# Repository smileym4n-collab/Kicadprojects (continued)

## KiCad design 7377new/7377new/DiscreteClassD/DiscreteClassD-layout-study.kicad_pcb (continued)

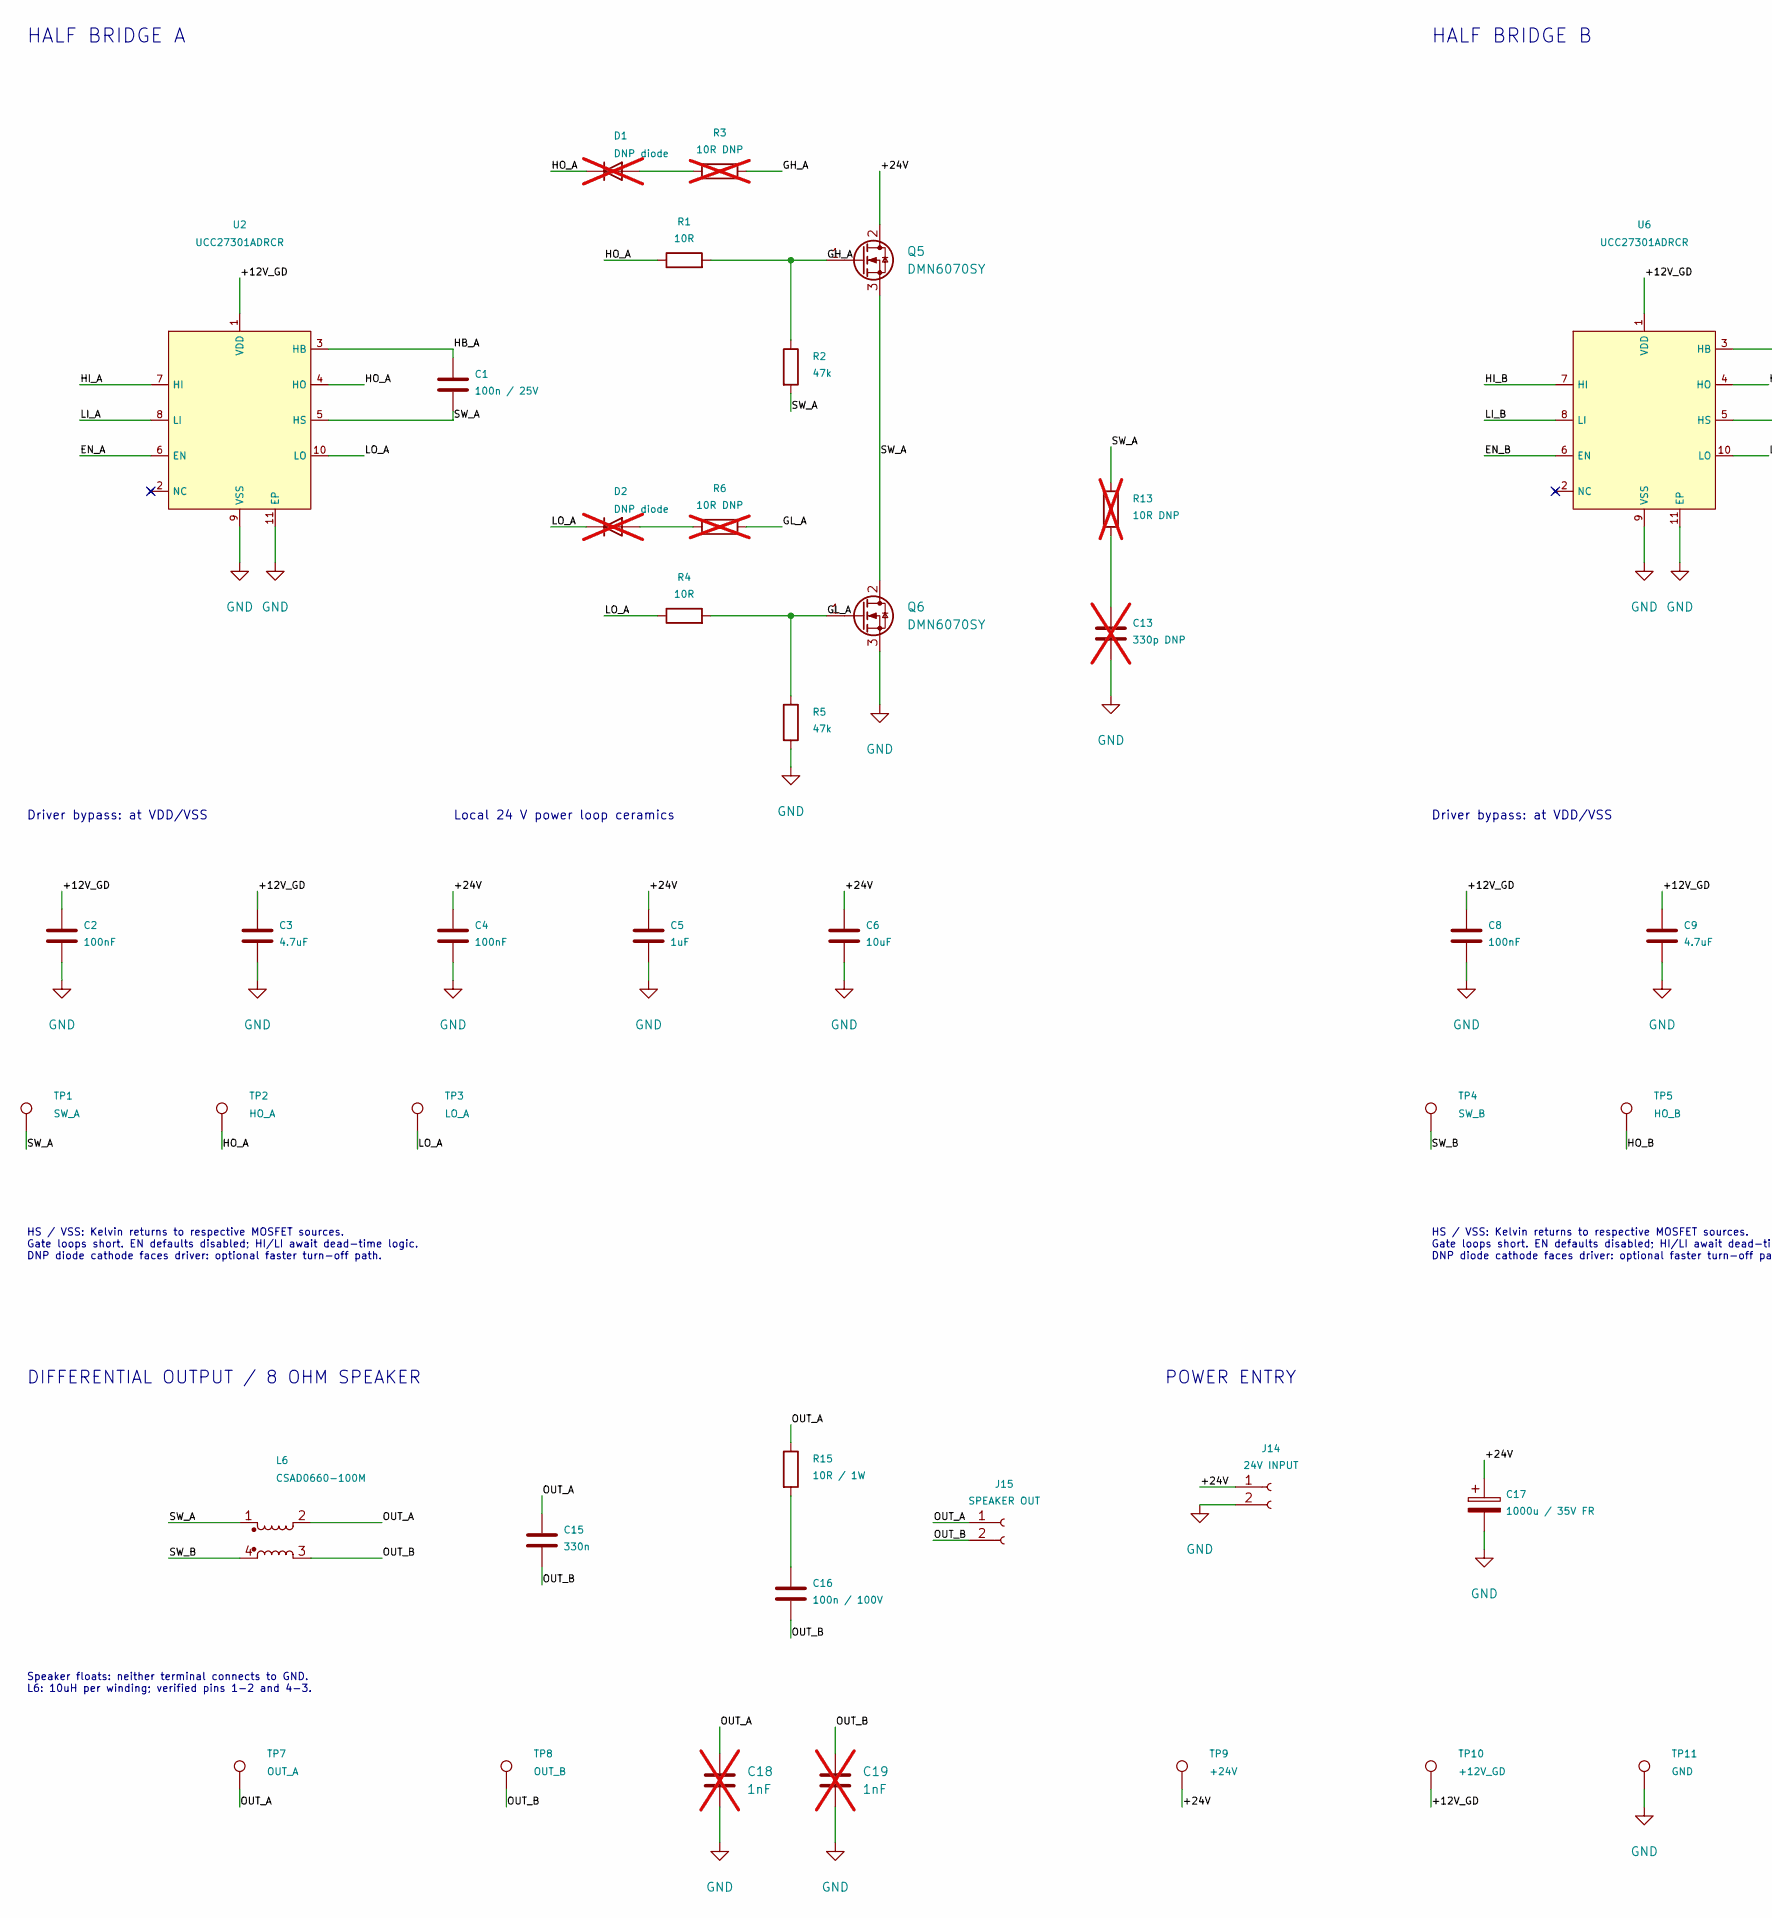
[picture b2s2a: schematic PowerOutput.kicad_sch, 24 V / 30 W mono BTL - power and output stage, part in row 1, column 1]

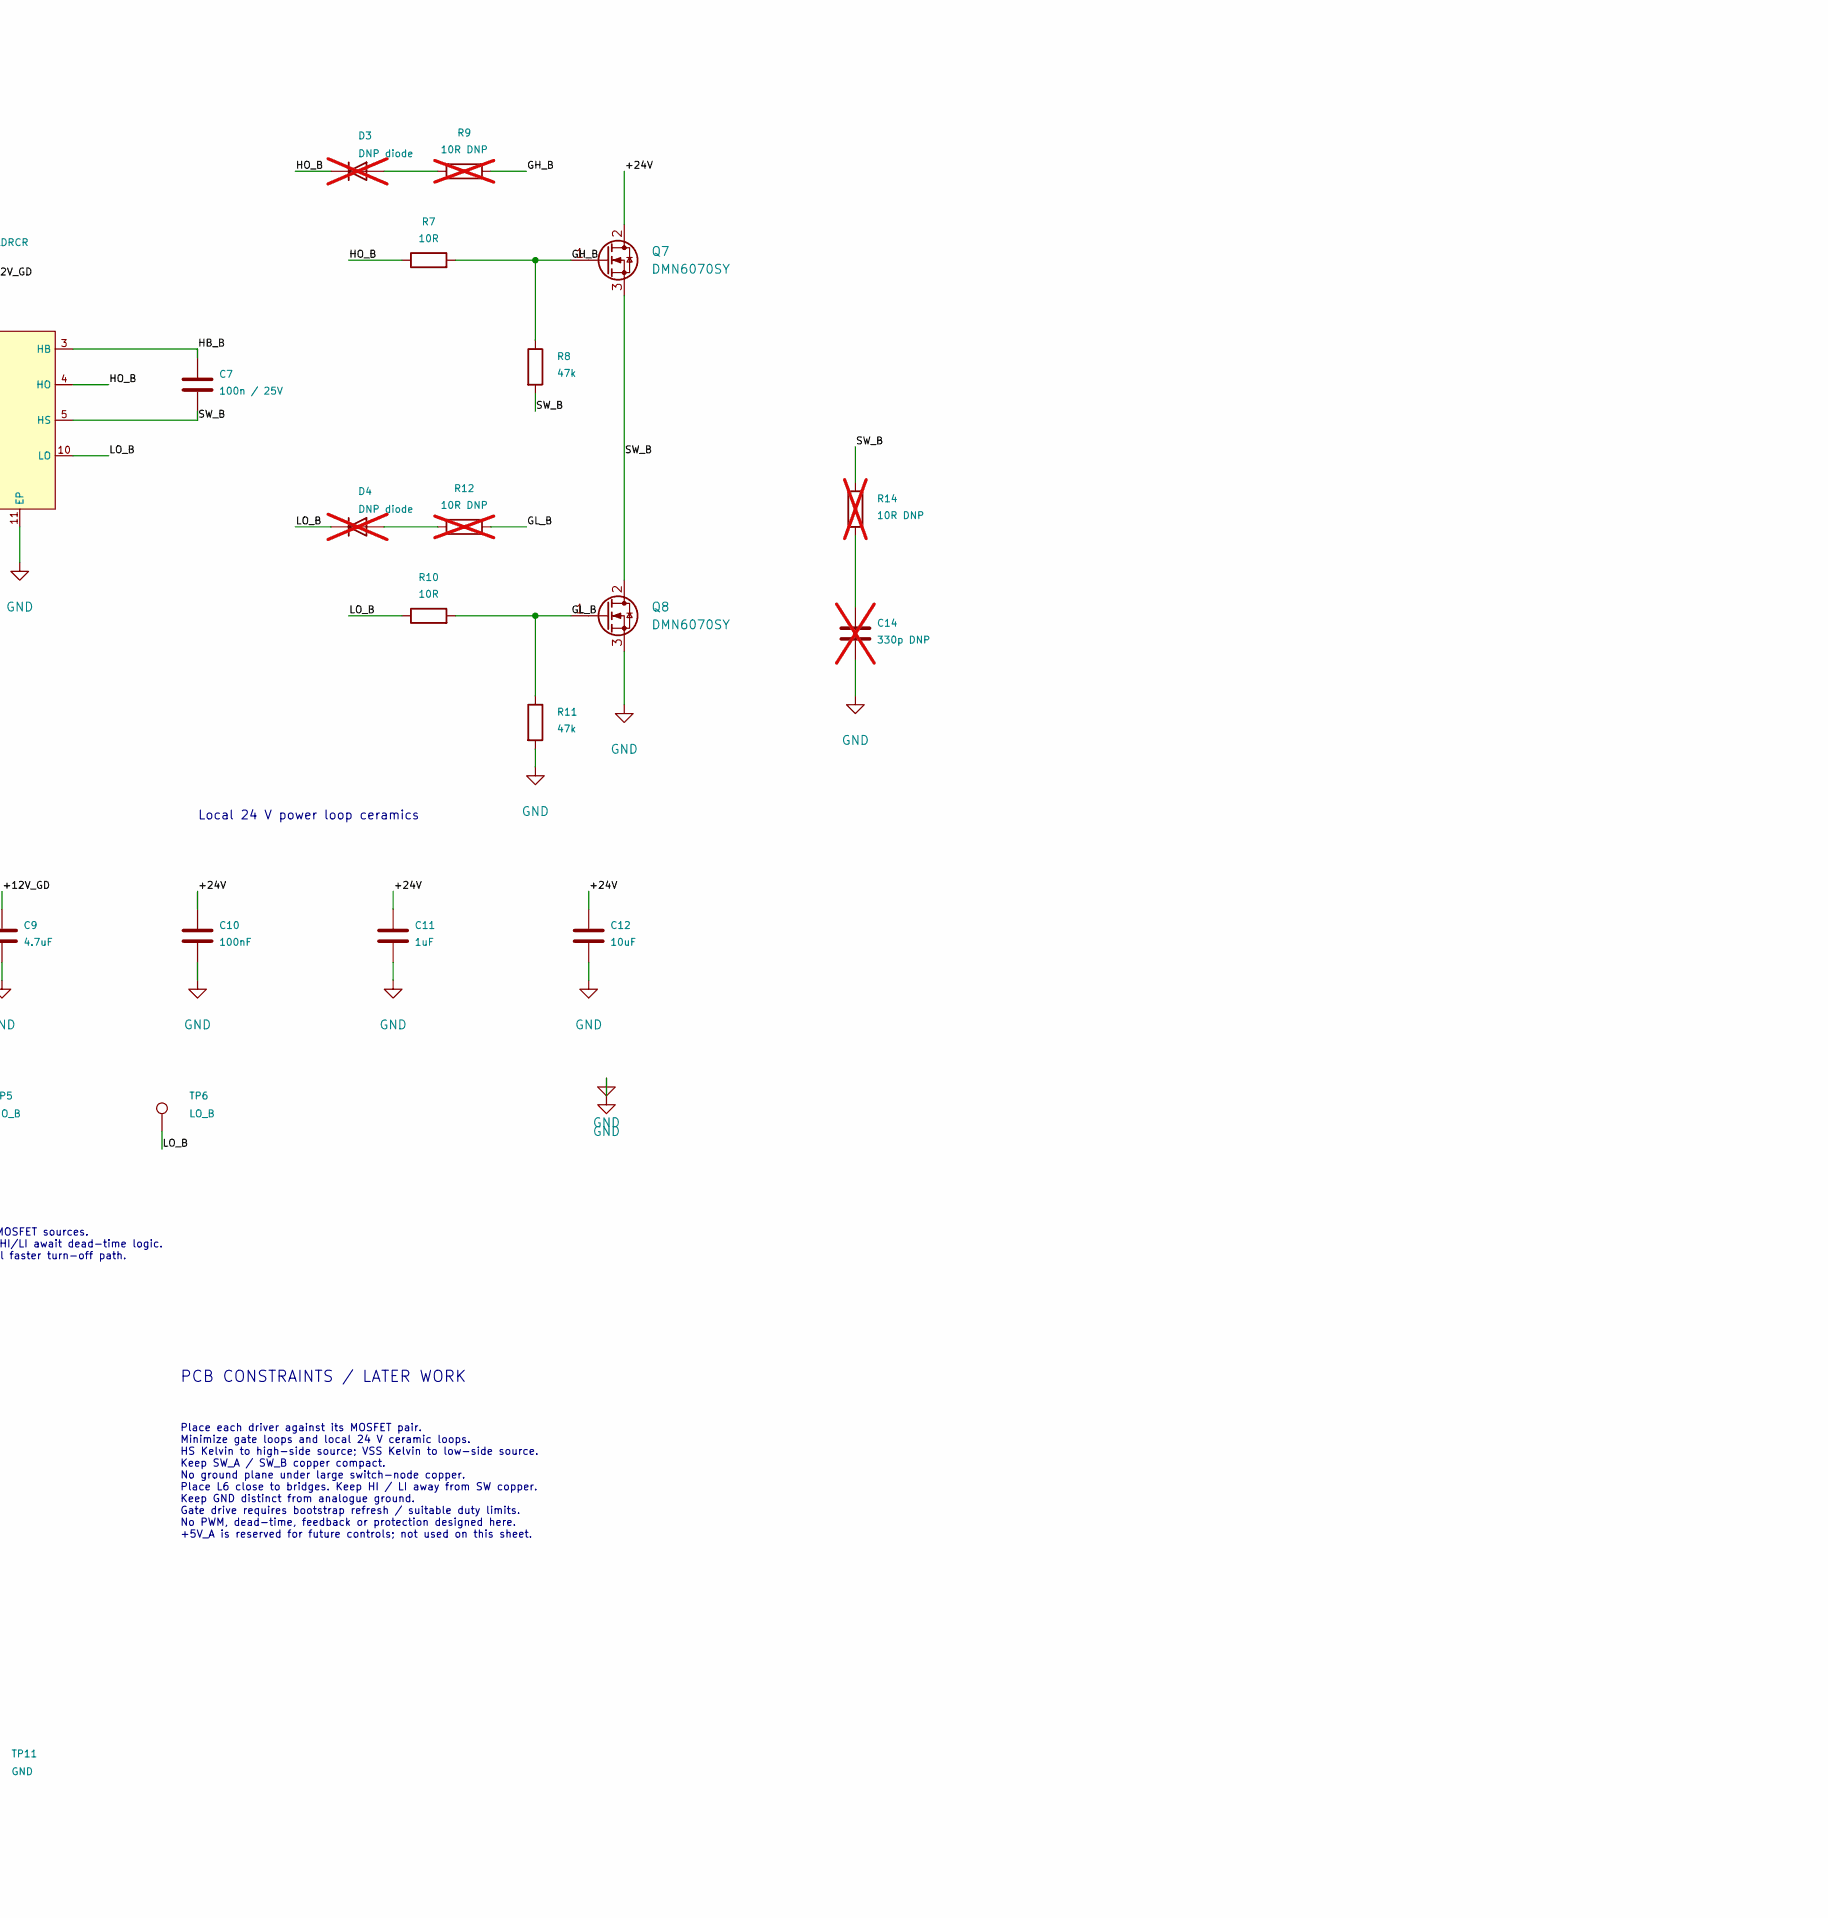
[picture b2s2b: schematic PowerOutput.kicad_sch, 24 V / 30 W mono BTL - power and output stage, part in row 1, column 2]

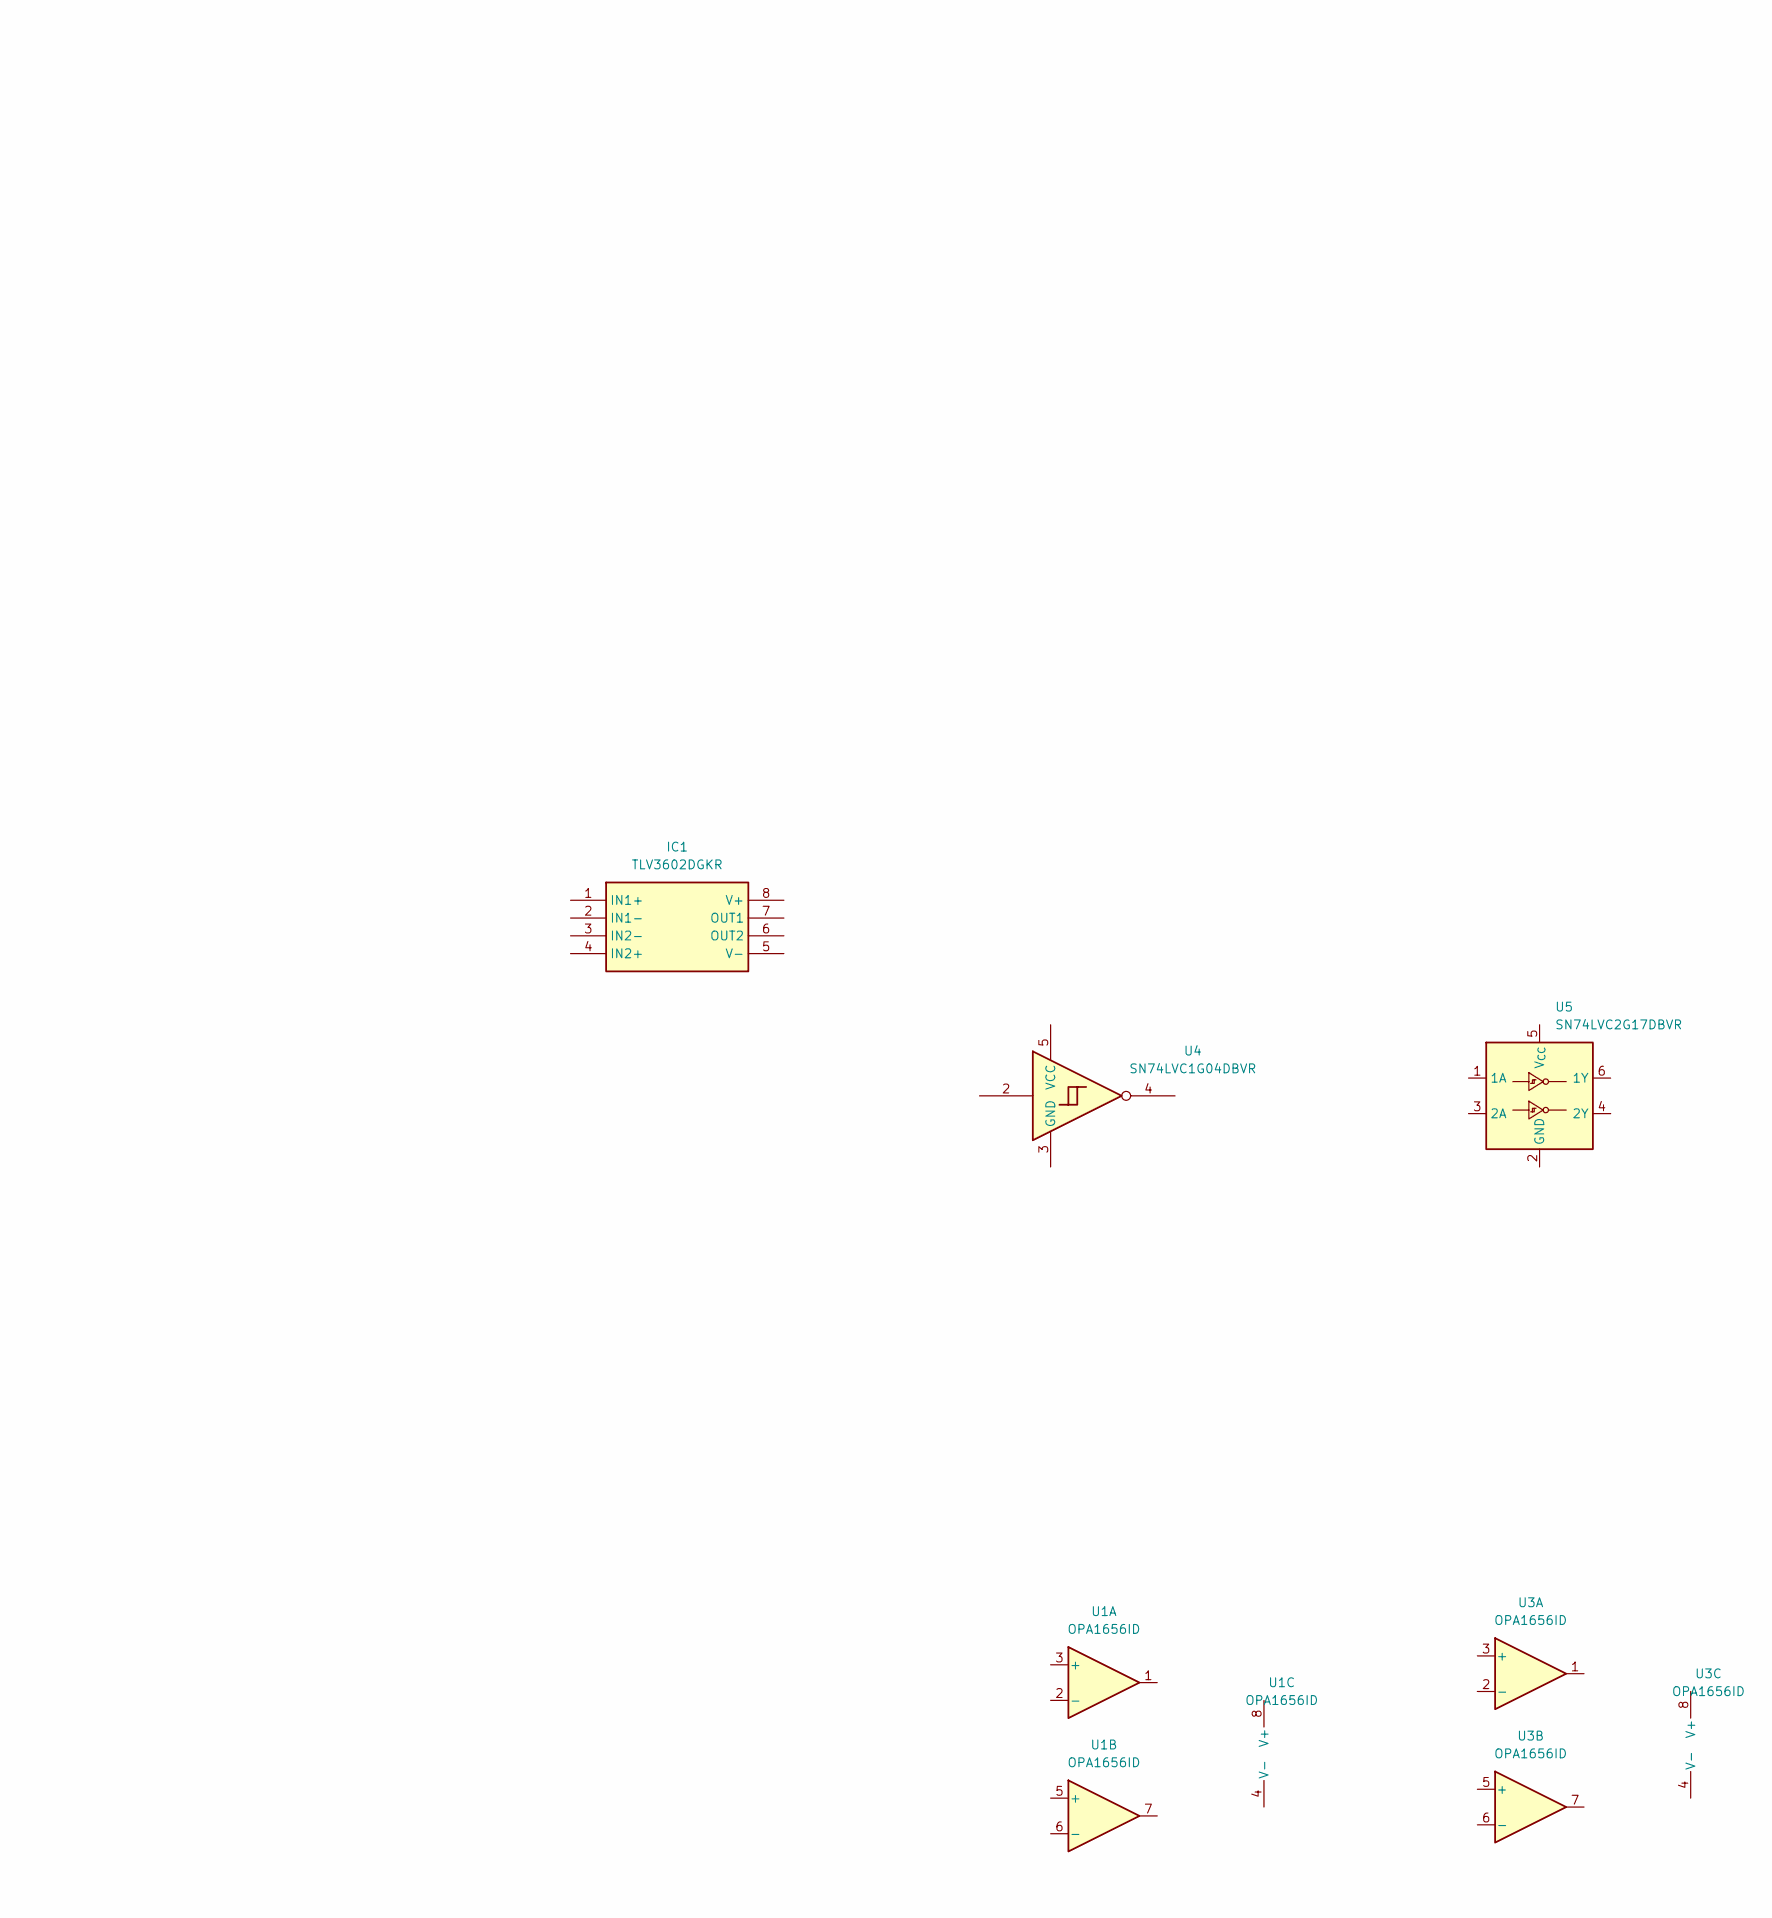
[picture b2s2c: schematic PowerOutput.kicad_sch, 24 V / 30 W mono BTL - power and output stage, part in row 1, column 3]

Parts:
C1, C7: 100n / 25V; C_0805_2012Metric
C2, C8: 100nF; C_0805_2012Metric
C3, C9: 4.7uF; C_0805_2012Metric
C4, C10: 100nF; C_1206_3216Metric_Pad1.33x1.80mm_HandSolder
C5, C11: 1uF; C_1206_3216Metric_Pad1.33x1.80mm_HandSolder
C6, C12: 10uF; C_1206_3216Metric_Pad1.33x1.80mm_HandSolder
C13, C14: 330p DNP; C_0805_2012Metric; Voltage 100V; not fitted
C15: 330n; C_Rect_L7.2mm_W3.0mm_P5.00mm_FKS2_FKP2_MKS2_MKP2; Voltage 100V
C16: 100n / 100V; C_1206_3216Metric_Pad1.33x1.80mm_HandSolder
C17: 1000u / 35V FR; CP_Radial_D12.5mm_P5.00mm; MPN EEUFR1V102
C18, C19: 1nF; C_0805_2012Metric_Pad1.18x1.45mm_HandSolder; not fitted
D1, D2, D3, D4: DNP diode; D_SOD-123; not fitted
IC1: TLV3602DGKR; VSSOP-8_3x3mm_P0.65mm; Mouser Part Number 595-TLV3602DGKR
J14: 24V INPUT; Molex_KK-396_A-41791-0002_1x02_P3.96mm_Vertical
J15: SPEAKER OUT; Molex_KK-396_A-41791-0002_1x02_P3.96mm_Vertical
L6: CSAD0660-100M
Q5, Q6, Q7, Q8: DMN6070SY; SOT-89-3
R1, R4, R7, R10: 10R; R_0805_2012Metric
R2, R5, R8, R11: 47k; R_0805_2012Metric
R3, R6, R9, R12: 10R DNP; R_0805_2012Metric; not fitted
R13, R14: 10R DNP; R_1206_3216Metric; not fitted
R15: 10R / 1W; R_2512_6332Metric
TP1: SW_A; TestPoint_Pad_D1.5mm
TP2: HO_A; TestPoint_Pad_D1.5mm
TP3: LO_A; TestPoint_Pad_D1.5mm
TP4: SW_B; TestPoint_Pad_D1.5mm
TP5: HO_B; TestPoint_Pad_D1.5mm
TP6: LO_B; TestPoint_Pad_D1.5mm
TP7: OUT_A; TestPoint_Pad_D1.5mm
TP8: OUT_B; TestPoint_Pad_D1.5mm
TP9: +24V; TestPoint_Pad_D1.5mm
TP10: +12V_GD; TestPoint_Pad_D1.5mm
TP11: GND; TestPoint_Pad_D1.5mm
U1, U3: OPA1656ID; SOIC-8_3.9x4.9mm_P1.27mm
U2, U6: UCC27301ADRCR; VSON-10-1EP_3x3mm_P0.5mm_EP1.65x2.4mm
U4: SN74LVC1G04DBVR; SOT-553
U5: SN74LVC2G17DBVR; SOT-23-6

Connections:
+5V_A: U4.5 (VCC), U5.5 (VCC); also elsewhere on the board
+12V_A: U1.8 (V+), U3.8 (V+); also elsewhere on the board
+12V_GD: C2.1, C3.1, C8.1, C9.1, TP10.1 (1_1), U2.1 (VDD), U6.1 (VDD); also elsewhere on the board
+24V: C4.1, C5.1, C6.1, C10.1, C11.1, C12.1, C17.1, J14.1, Q5.2 (D), Q7.2 (D), TP9.1; also elsewhere on the board
/LEFT OUTPUT/OUT_A: C15.1, C18.1, J15.1, L6.2, R15.1, TP7.1 (1_1)
/LEFT OUTPUT/OUT_B: C15.2, C16.2, C19.1, J15.2, L6.3, TP8.1 (1_1)
/LEFT OUTPUT/SW_A: C1.2, L6.1, Q5.3 (S), Q6.2 (D), R2.2, R13.1, TP1.1 (1_1), U2.5 (HS)
/LEFT OUTPUT/SW_B: C7.2, L6.4, Q7.3 (S), Q8.2 (D), R8.2, R14.1, TP4.1 (1_1), U6.5 (HS)
/PWM_L: U4.2; also elsewhere on the board
/TRIANGLE_400K: U3.7; also elsewhere on the board
/VREF_2V5: U3.1, U3.2 (-), U3.5 (+); also elsewhere on the board
GND: C2.2, C3.2, C4.2, C5.2, C6.2, C8.2, C9.2, C10.2, C11.2, C12.2, C13.2, C14.2, C17.2, C18.2, C19.2, J14.2, Q6.3 (S), Q8.3 (S), R5.2, R11.2, TP11.1, U1.4 (V-), U2.9 (VSS), U2.11 (EP), U3.4 (V-), U4.3 (GND), U5.2 (GND), U6.9 (VSS), U6.11 (EP); also elsewhere on the board
unnamed: C13.1, R13.2
unnamed: C14.1, R14.2
unnamed: C16.1, R15.2
unnamed: D1.2 (A), R3.1
unnamed: D1.1 (K), R1.1, TP2.1 (1_1), U2.4 (HO)
unnamed: D2.2 (A), R6.1
unnamed: D2.1 (K), R4.1, TP3.1 (1_1), U2.10 (LO)
unnamed: D3.2 (A), R9.1
unnamed: D3.1 (K), R7.1, TP5.1 (1_1), U6.4 (HO)
unnamed: D4.2 (A), R12.1
unnamed: D4.1 (K), R10.1, TP6.1 (1_1), U6.10 (LO)
unnamed 41: U5.1 (1A); also elsewhere on the board
unnamed 42: U5.3 (2A); also elsewhere on the board
unnamed 43: U4.4; also elsewhere on the board
unnamed: Q5.1 (G), R1.2, R2.1, R3.2
unnamed: Q6.1 (G), R4.2, R5.1, R6.2
unnamed: Q7.1 (G), R7.2, R8.1, R9.2
unnamed: Q8.1 (G), R10.2, R11.1, R12.2
unnamed 63: U1.3 (+); also elsewhere on the board
unnamed 64: U1.1, U1.2 (-); also elsewhere on the board
unnamed 65: U1.5 (+); also elsewhere on the board
unnamed 66: U1.6 (-), U1.7; also elsewhere on the board
unnamed: C1.1, U2.3 (HB)
unnamed 68: U3.3 (+); also elsewhere on the board
unnamed 69: U3.6 (-); also elsewhere on the board
unnamed: C7.1, U6.3 (HB)

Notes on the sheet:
HALF BRIDGE A
PCB CONSTRAINTS / LATER WORK
POWER ENTRY
Local 24 V power loop ceramics
HS / VSS: Kelvin returns to respective MOSFET sources. Gate loops short. EN defaults disabled; HI/LI await dead-time logic. DNP diode cathode faces driver: optional faster turn-off path.
Speaker floats: neither terminal connects to GND. L6: 10uH per winding; verified pins 1-2 and 4-3.
HALF BRIDGE B
DIFFERENTIAL OUTPUT / 8 OHM SPEAKER
Driver bypass: at VDD/VSS
Place each driver against its MOSFET pair. Minimize gate loops and local 24 V ceramic loops. HS Kelvin to high-side source; VSS Kelvin to low-side source. Keep SW_A / SW_B copper compact. No ground plane under large switch-node copper. Place L6 close to bridges. Keep HI / LI away from SW copper. Ke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

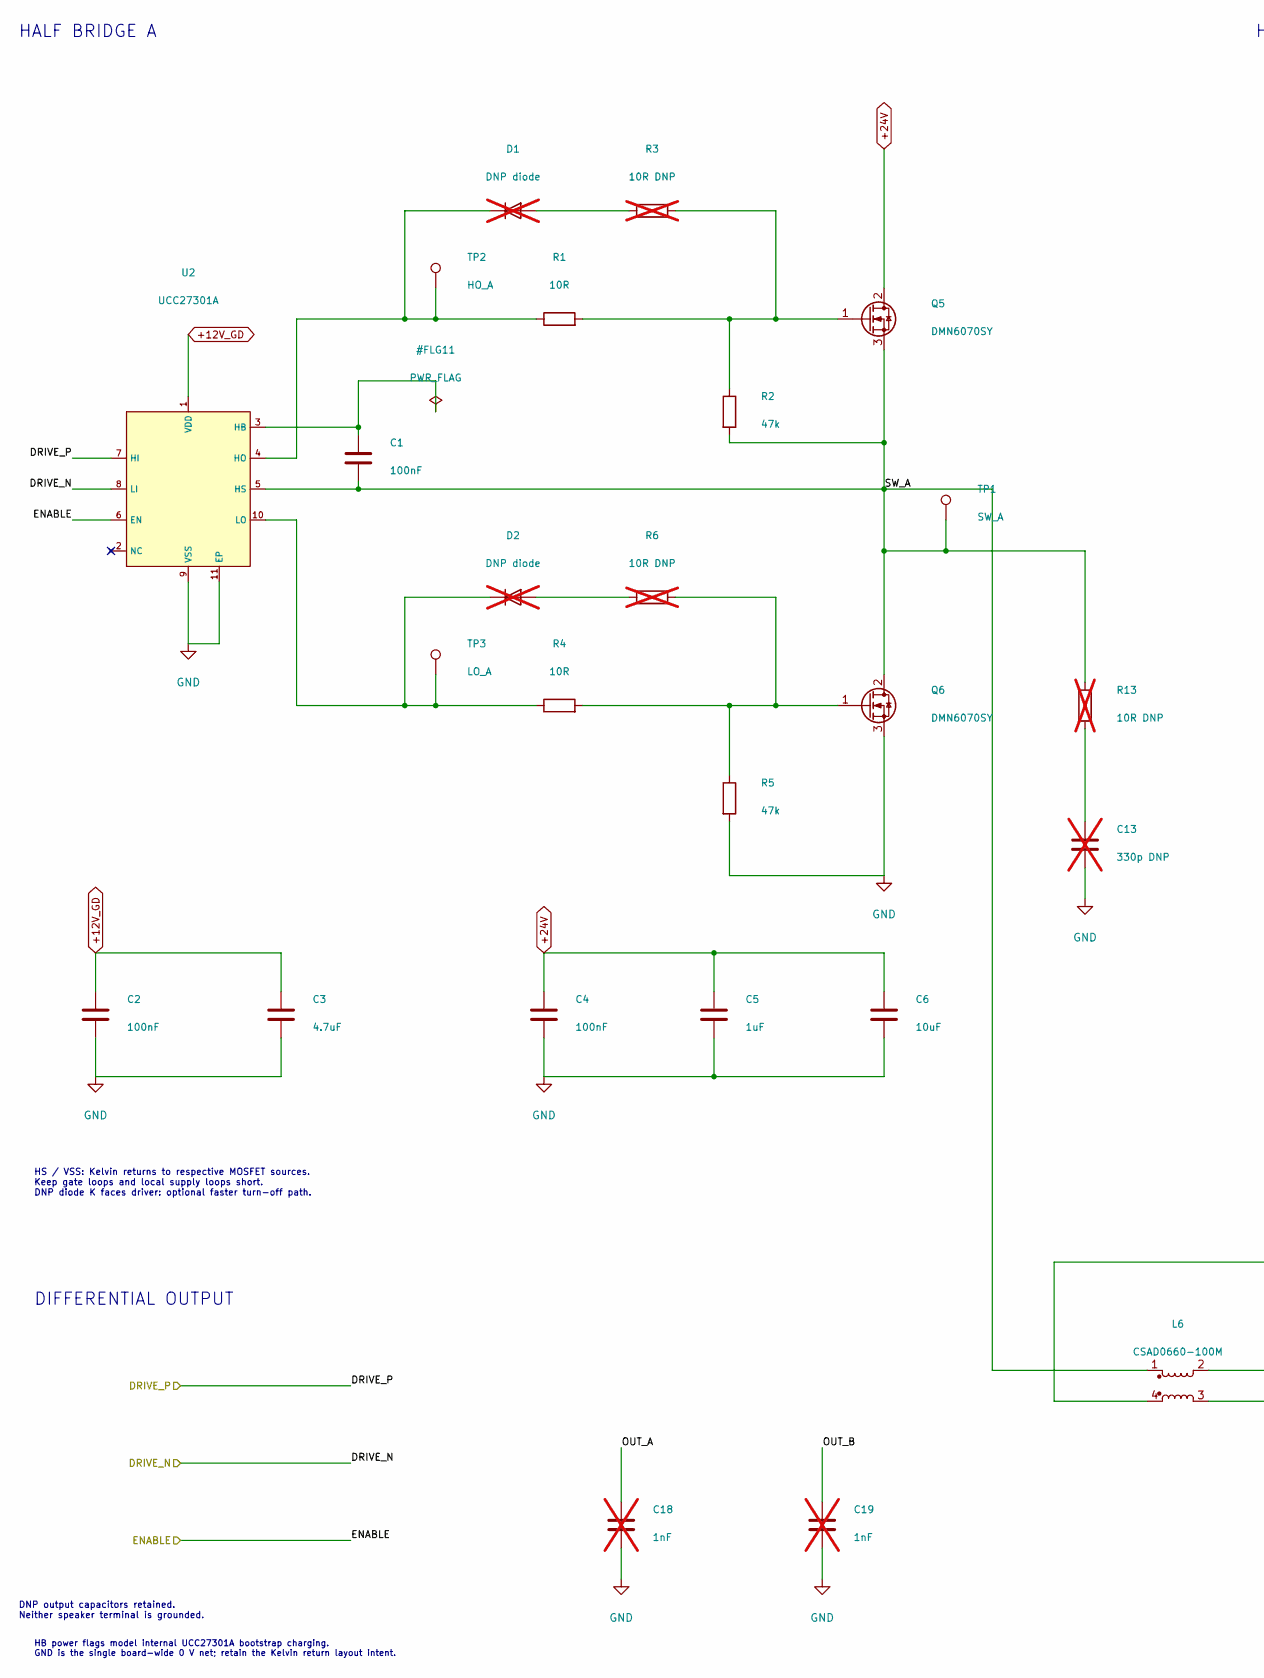
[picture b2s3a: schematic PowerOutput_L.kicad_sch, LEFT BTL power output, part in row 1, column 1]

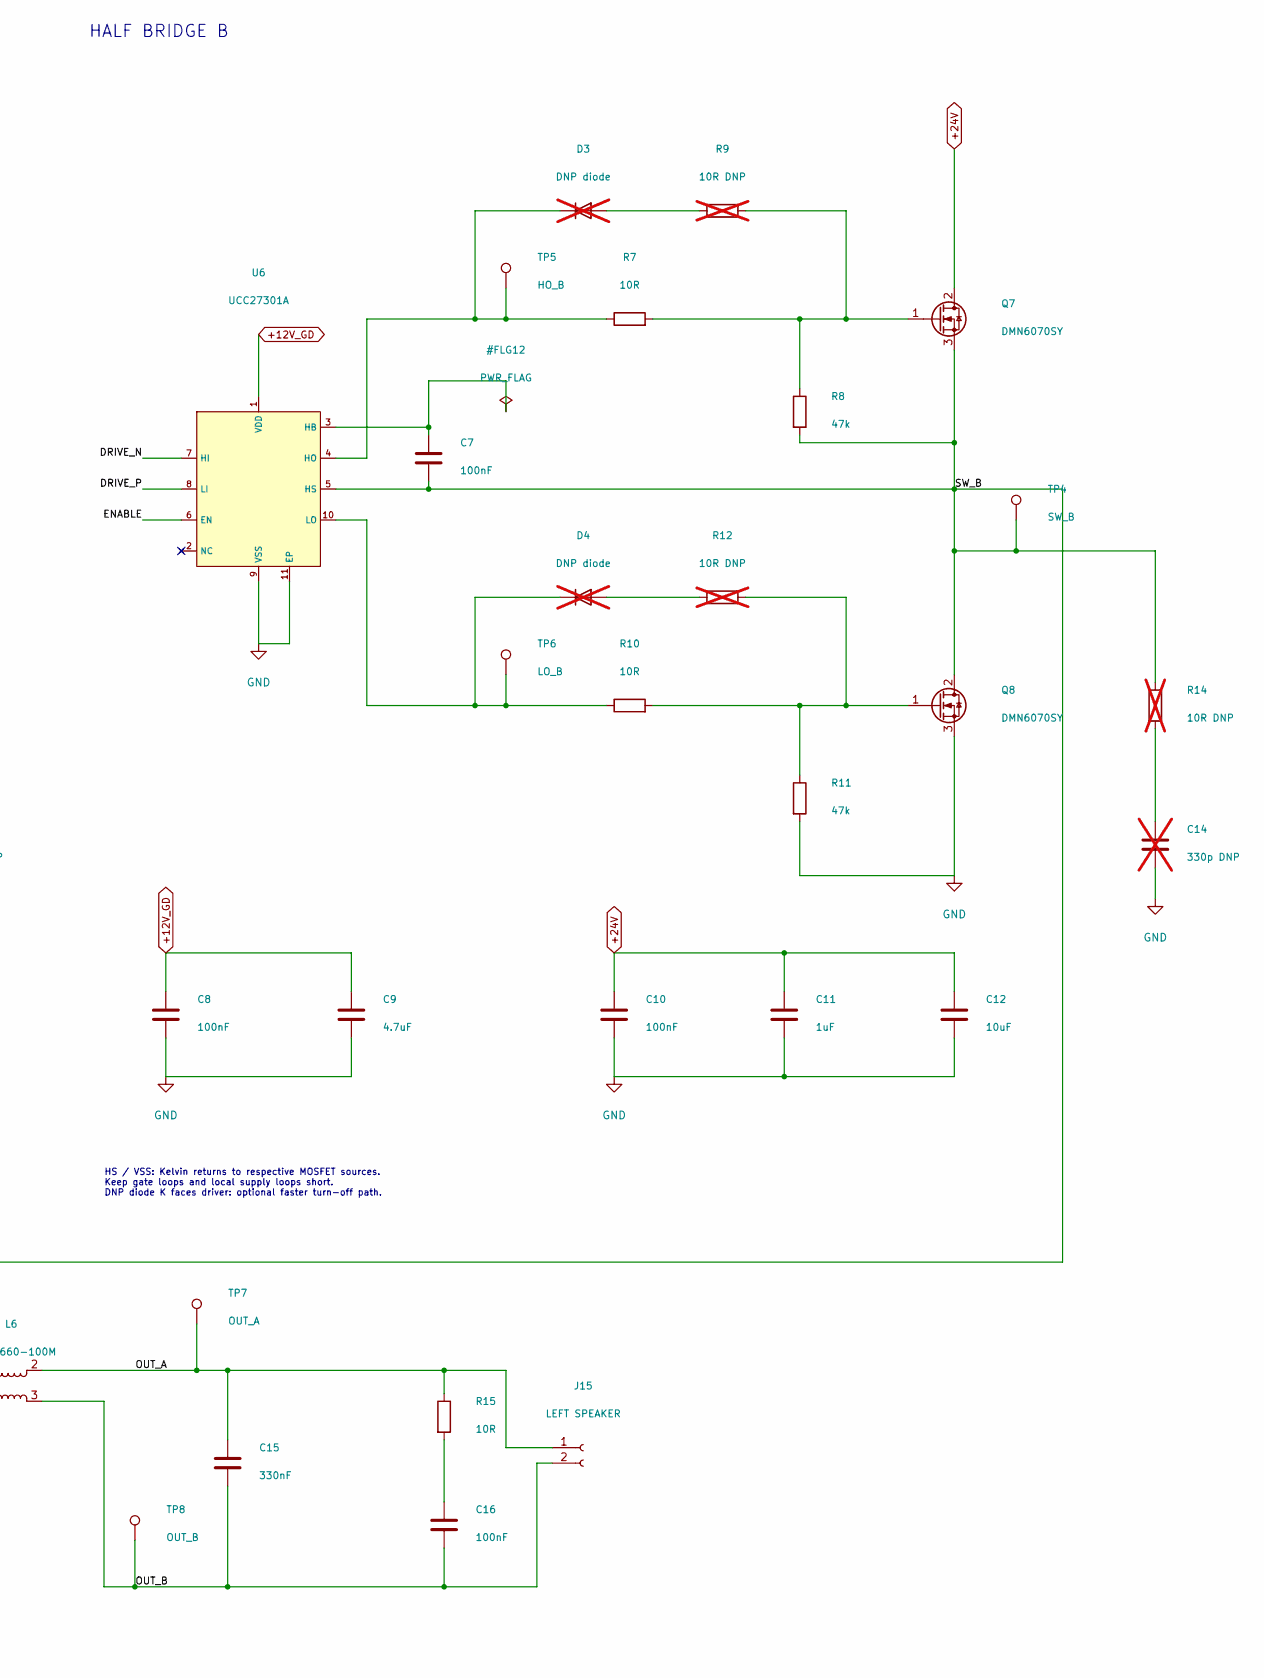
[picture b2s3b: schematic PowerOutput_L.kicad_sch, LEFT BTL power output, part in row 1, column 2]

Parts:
C1, C2, C7, C8: 100nF; C_0805_2012Metric
C3, C9: 4.7uF; C_0805_2012Metric
C4, C10, C16: 100nF; C_1206_3216Metric_Pad1.33x1.80mm_HandSolder
C5, C11: 1uF; C_1206_3216Metric_Pad1.33x1.80mm_HandSolder
C6, C12: 10uF; C_1206_3216Metric_Pad1.33x1.80mm_HandSolder
C13, C14: 330p DNP; C_0805_2012Metric; Voltage 100V; not fitted
C15: 330nF; C_Rect_L7.2mm_W3.0mm_P5.00mm_FKS2_FKP2_MKS2_MKP2; Voltage 100V
C18, C19: 1nF; C_0805_2012Metric_Pad1.18x1.45mm_HandSolder; not fitted
D1, D2, D3, D4: DNP diode; D_SOD-123; not fitted
J15: LEFT SPEAKER; Molex_KK-396_A-41791-0002_1x02_P3.96mm_Vertical
L6: CSAD0660-100M
Q5, Q6, Q7, Q8: DMN6070SY; SOT-89-3
R1, R4, R7, R10: 10R; R_0805_2012Metric
R2, R5, R8, R11: 47k; R_0805_2012Metric
R3, R6, R9, R12: 10R DNP; R_0805_2012Metric; not fitted
R13, R14: 10R DNP; R_1206_3216Metric; not fitted
R15: 10R; R_2512_6332Metric
TP1: SW_A; TestPoint_Pad_D1.5mm
TP2: HO_A; TestPoint_Pad_D1.5mm
TP3: LO_A; TestPoint_Pad_D1.5mm
TP4: SW_B; TestPoint_Pad_D1.5mm
TP5: HO_B; TestPoint_Pad_D1.5mm
TP6: LO_B; TestPoint_Pad_D1.5mm
TP7: OUT_A; TestPoint_Pad_D1.5mm
TP8: OUT_B; TestPoint_Pad_D1.5mm
U2, U6: UCC27301A; VSON-10-1EP_3x3mm_P0.5mm_EP1.65x2.4mm

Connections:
+12V_GD: C2.1, C3.1, C8.1, C9.1, U2.1 (VDD), U6.1 (VDD); also elsewhere on the board
+24V: C4.1, C5.1, C6.1, C10.1, C11.1, C12.1, Q5.2 (D), Q7.2 (D); also elsewhere on the board
/LEFT OUTPUT/OUT_A: C15.1, C18.1, J15.1, L6.2, R15.1, TP7.1 (1_1)
/LEFT OUTPUT/OUT_B: C15.2, C16.2, C19.1, J15.2, L6.3, TP8.1 (1_1)
/LEFT OUTPUT/SW_A: C1.2, L6.1, Q5.3 (S), Q6.2 (D), R2.2, R13.1, TP1.1 (1_1), U2.5 (HS)
/LEFT OUTPUT/SW_B: C7.2, L6.4, Q7.3 (S), Q8.2 (D), R8.2, R14.1, TP4.1 (1_1), U6.5 (HS)
GND: C2.2, C3.2, C4.2, C5.2, C6.2, C8.2, C9.2, C10.2, C11.2, C12.2, C13.2, C14.2, C18.2, C19.2, Q6.3 (S), Q8.3 (S), R5.2, R11.2, U2.9 (VSS), U2.11 (EP), U6.9 (VSS), U6.11 (EP); also elsewhere on the board
unnamed: C13.1, R13.2
unnamed: C14.1, R14.2
unnamed: C16.1, R15.2
unnamed: D1.2 (A), R3.1
unnamed: D1.1 (K), R1.1, TP2.1 (1_1), U2.4 (HO)
unnamed: D2.2 (A), R6.1
unnamed: D2.1 (K), R4.1, TP3.1 (1_1), U2.10 (LO)
unnamed: D3.2 (A), R9.1
unnamed: D3.1 (K), R7.1, TP5.1 (1_1), U6.4 (HO)
unnamed: D4.2 (A), R12.1
unnamed: D4.1 (K), R10.1, TP6.1 (1_1), U6.10 (LO)
unnamed: Q5.1 (G), R1.2, R2.1, R3.2
unnamed: Q6.1 (G), R4.2, R5.1, R6.2
unnamed: Q7.1 (G), R7.2, R8.1, R9.2
unnamed: Q8.1 (G), R10.2, R11.1, R12.2
unnamed: C1.1, U2.3 (HB)
unnamed: C7.1, U6.3 (HB)

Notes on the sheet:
DNP output capacitors retained. Neither speaker terminal is grounded.
HS / VSS: Kelvin returns to respective MOSFET sources. Keep gate loops and local supply loops short. DNP diode K faces driver: optional faster turn-off path.
DIFFERENTIAL OUTPUT
HB power flags model internal UCC27301A bootstrap charging. GND is the single board-wide 0 V net; retain the Kelvin return layout intent.
HALF BRIDGE B
HALF BRIDGE A
